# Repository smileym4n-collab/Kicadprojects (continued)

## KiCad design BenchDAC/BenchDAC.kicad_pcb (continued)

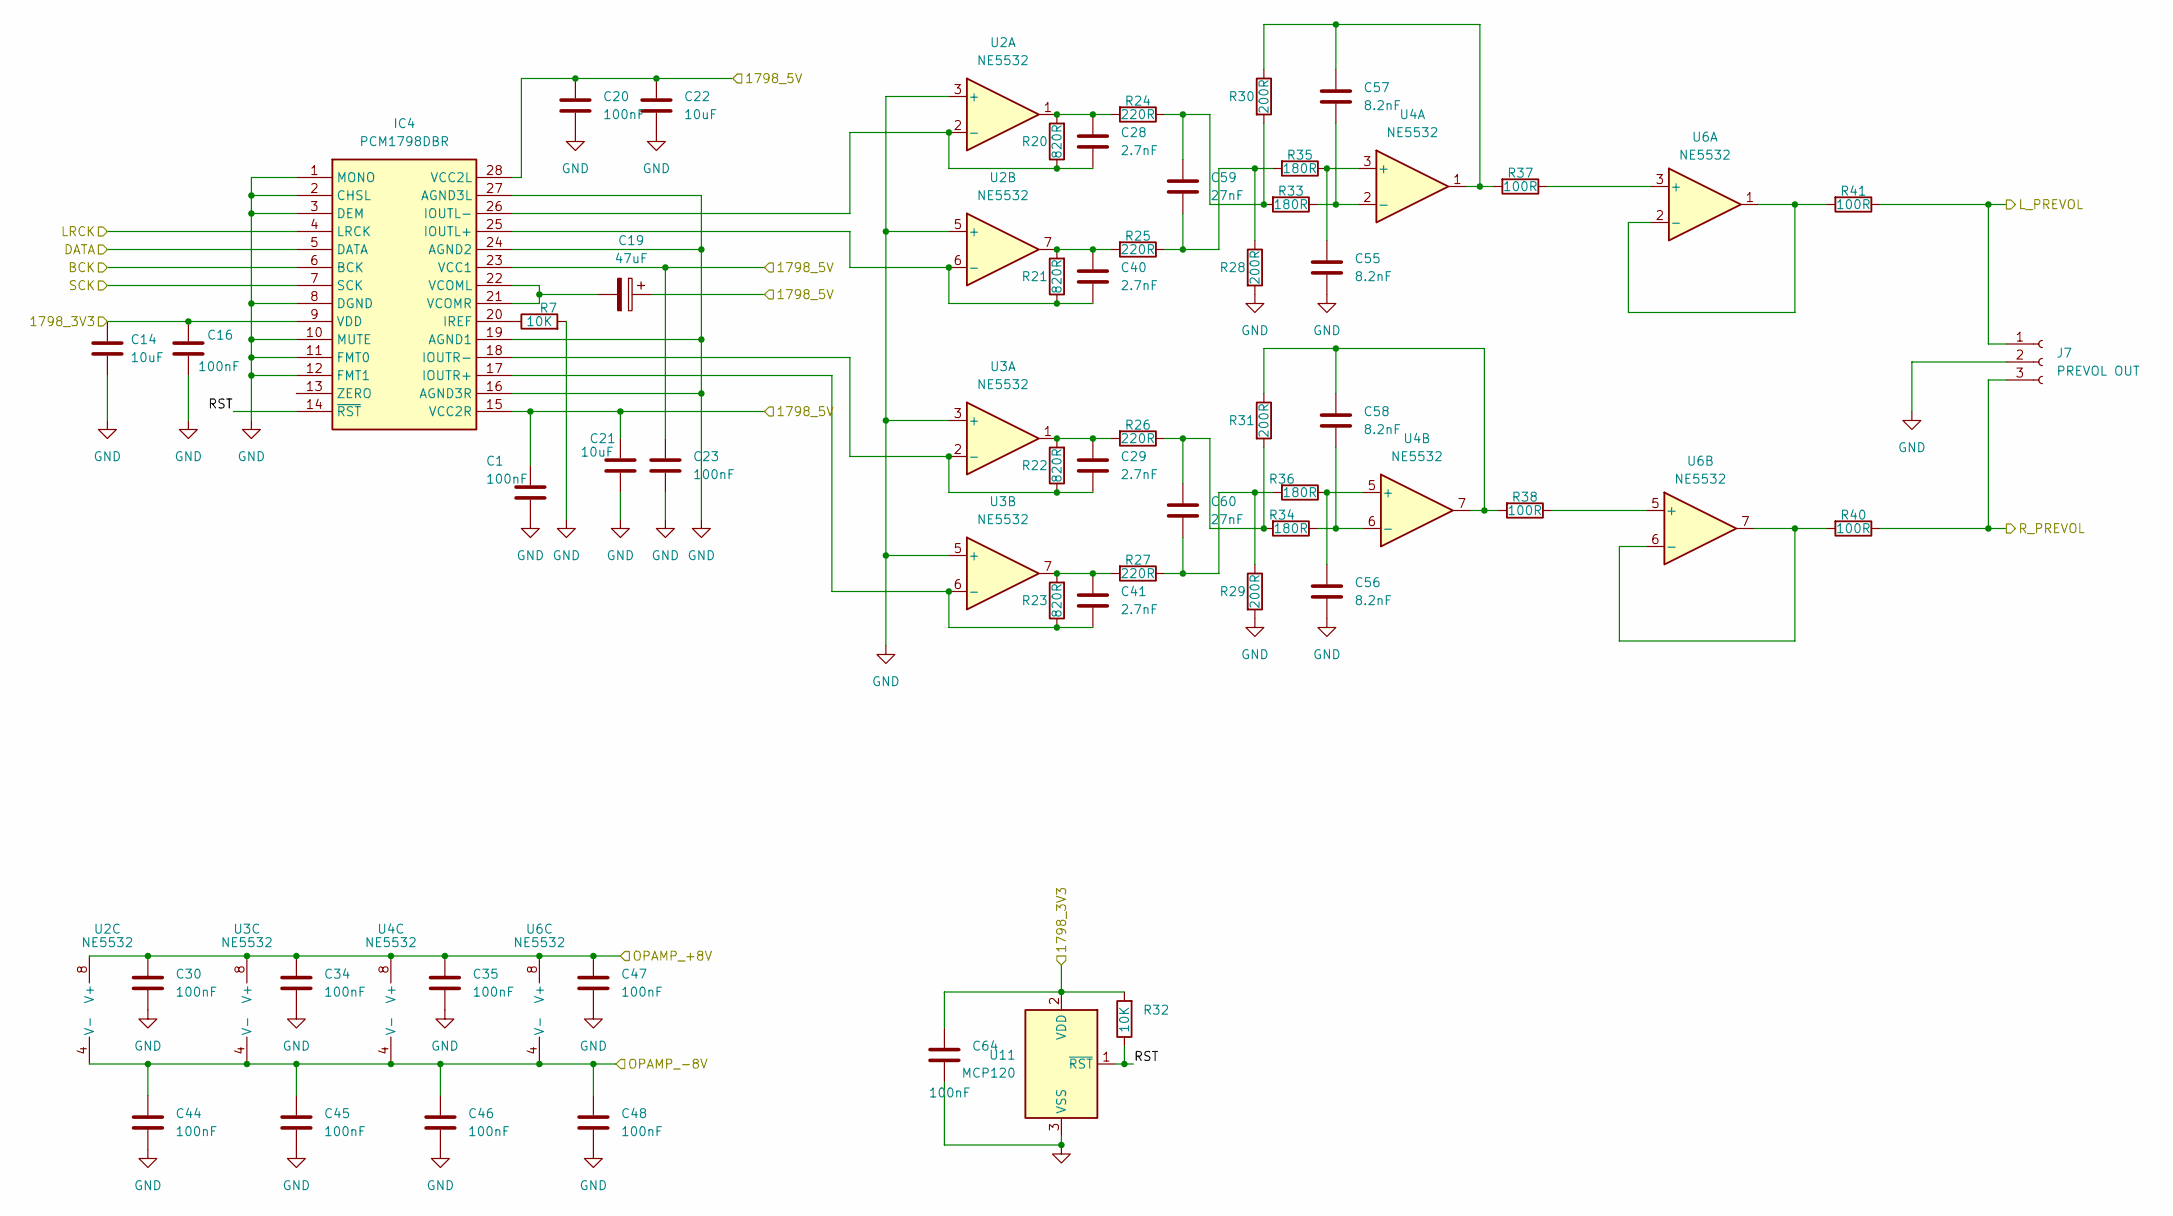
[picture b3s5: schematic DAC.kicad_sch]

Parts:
C1, C16, C20, C23, C30, C34, C35, C44, C45, C46, C47, C48, C64: 100nF; C_0603_1608Metric_Pad1.08x0.95mm_HandSolder
C14, C21, C22: 10uF; C_0805_2012Metric_Pad1.18x1.45mm_HandSolder
C19: 47uF; CP_Radial_D6.3mm_P2.50mm
C28, C29, C40, C41: 2.7nF; C_0805_2012Metric_Pad1.18x1.45mm_HandSolder
C55, C56, C57, C58: 8.2nF; C_0805_2012Metric_Pad1.18x1.45mm_HandSolder
C59, C60: 27nF; C_1206_3216Metric_Pad1.33x1.80mm_HandSolder
IC4: PCM1798DBR; SOP65P780X200-28N; Mouser Part Number 595-PCM1798DBR
J7: PREVOL OUT; JST_XH_B3B-XH-A_1x03_P2.50mm_Vertical
R7: 10K; R_0603_1608Metric_Pad0.98x0.95mm_HandSolder
R20, R21, R22, R23: 820R; R_0805_2012Metric_Pad1.20x1.40mm_HandSolder
R24, R25, R26, R27: 220R; R_0805_2012Metric_Pad1.20x1.40mm_HandSolder
R28, R29, R30, R31: 200R; R_0805_2012Metric_Pad1.20x1.40mm_HandSolder
R32: 10K; R_0805_2012Metric_Pad1.20x1.40mm_HandSolder
R33, R34, R35, R36: 180R; R_0805_2012Metric_Pad1.20x1.40mm_HandSolder
R37, R38, R40, R41: 100R; R_0805_2012Metric_Pad1.20x1.40mm_HandSolder
U2, U3, U4, U6: NE5532; SOIC-8_3.9x4.9mm_P1.27mm
U11: MCP120; SOT-23

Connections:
/DAC/1798_3V3: C14.1, C16.1, C64.2, IC4.9 (VDD), R32.2, U11.2 (VDD); also elsewhere on the board
/DAC/1798_5V: C1.1, C19.1, C20.1, C21.1, C22.1, C23.1, IC4.15 (VCC2R), IC4.23 (VCC1), IC4.28 (VCC2L); also elsewhere on the board
/DAC/BCK: IC4.6 (BCK); also elsewhere on the board
/DAC/DATA: IC4.5 (DATA); also elsewhere on the board
/DAC/LRCK: IC4.4 (LRCK); also elsewhere on the board
/DAC/L_PREVOL: J7.1, R41.1; also elsewhere on the board
/DAC/OPAMP_+8V: C30.1, C34.1, C35.1, C47.1, U2.8 (V+), U3.8 (V+), U4.8 (V+), U6.8 (V+); also elsewhere on the board
/DAC/OPAMP_-8V: C44.1, C45.1, C46.1, C48.1, U2.4 (V-), U3.4 (V-), U4.4 (V-), U6.4 (V-); also elsewhere on the board
/DAC/RST: IC4.14 (~RST), R32.1, U11.1 (~RST)
/DAC/R_PREVOL: J7.3, R40.1; also elsewhere on the board
/DAC/SCK: IC4.7 (SCK); also elsewhere on the board
GND: C1.2, C14.2, C16.2, C20.2, C21.2, C22.2, C23.2, C30.2, C34.2, C35.2, C44.2, C45.2, C46.2, C47.2, C48.2, C55.2, C56.2, C64.1, IC4.1 (MONO), IC4.2 (CHSL), IC4.3 (DEM), IC4.8 (DGND), IC4.10 (MUTE), IC4.11 (FMT0), IC4.12 (FMT1), IC4.16 (AGND3R), IC4.19 (AGND1), IC4.24 (AGND2), IC4.27 (AGND3L), J7.2, R7.2, R28.2, R29.2, U2.3 (+), U2.5 (+), U3.3 (+), U3.5 (+), U11.3 (VSS); also elsewhere on the board
unnamed: C28.2, R20.2, R24.2, U2.1
unnamed: C29.2, R22.2, R26.2, U3.1
unnamed: C40.2, R21.2, R25.2, U2.7
unnamed: C41.2, R23.2, R27.2, U3.7
unnamed: C57.1, R30.1, R37.2, U4.1
unnamed: C58.1, R31.1, R38.2, U4.7
unnamed: C59.1, R24.1, R30.2, R33.2
unnamed: C59.2, R25.1, R28.1, R35.2
unnamed: C60.1, R26.1, R31.2, R34.2
unnamed: C60.2, R27.1, R29.1, R36.2
unnamed: C40.1, IC4.25 (IOUTL+), R21.1, U2.6 (-)
unnamed: C28.1, IC4.26 (IOUTL-), R20.1, U2.2 (-)
unnamed: C41.1, IC4.17 (IOUTR+), R23.1, U3.6 (-)
unnamed: C29.1, IC4.18 (IOUTR-), R22.1, U3.2 (-)
unnamed: IC4.20 (IREF), R7.1
unnamed: C19.2, IC4.21 (VCOMR), IC4.22 (VCOML)
unnamed: C55.1, R35.1, U4.3 (+)
unnamed: C57.2, R33.1, U4.2 (-)
unnamed: C56.1, R36.1, U4.5 (+)
unnamed: C58.2, R34.1, U4.6 (-)
unnamed: R37.1, U6.3 (+)
unnamed: R41.2, U6.1, U6.2 (-)
unnamed: R38.1, U6.5 (+)
unnamed: R40.2, U6.6 (-), U6.7

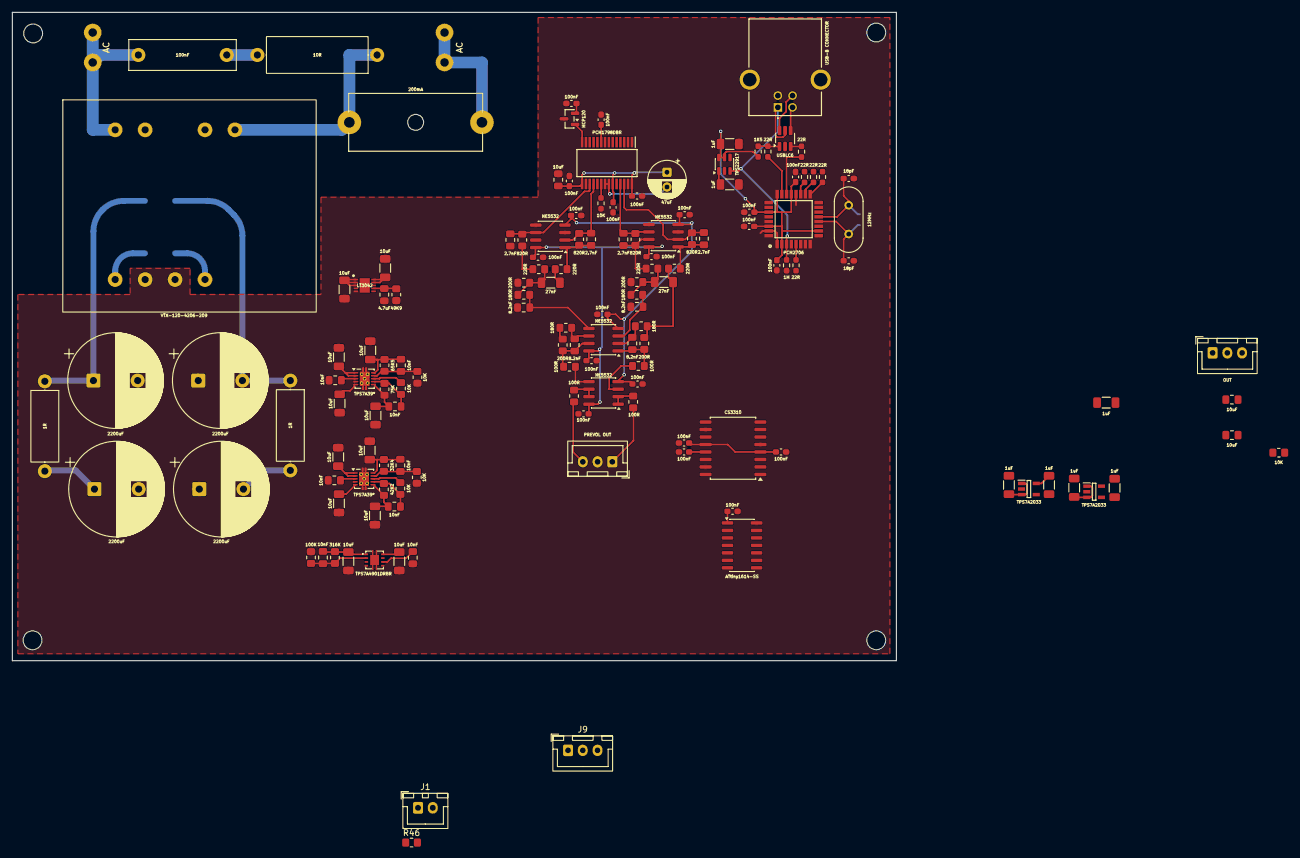
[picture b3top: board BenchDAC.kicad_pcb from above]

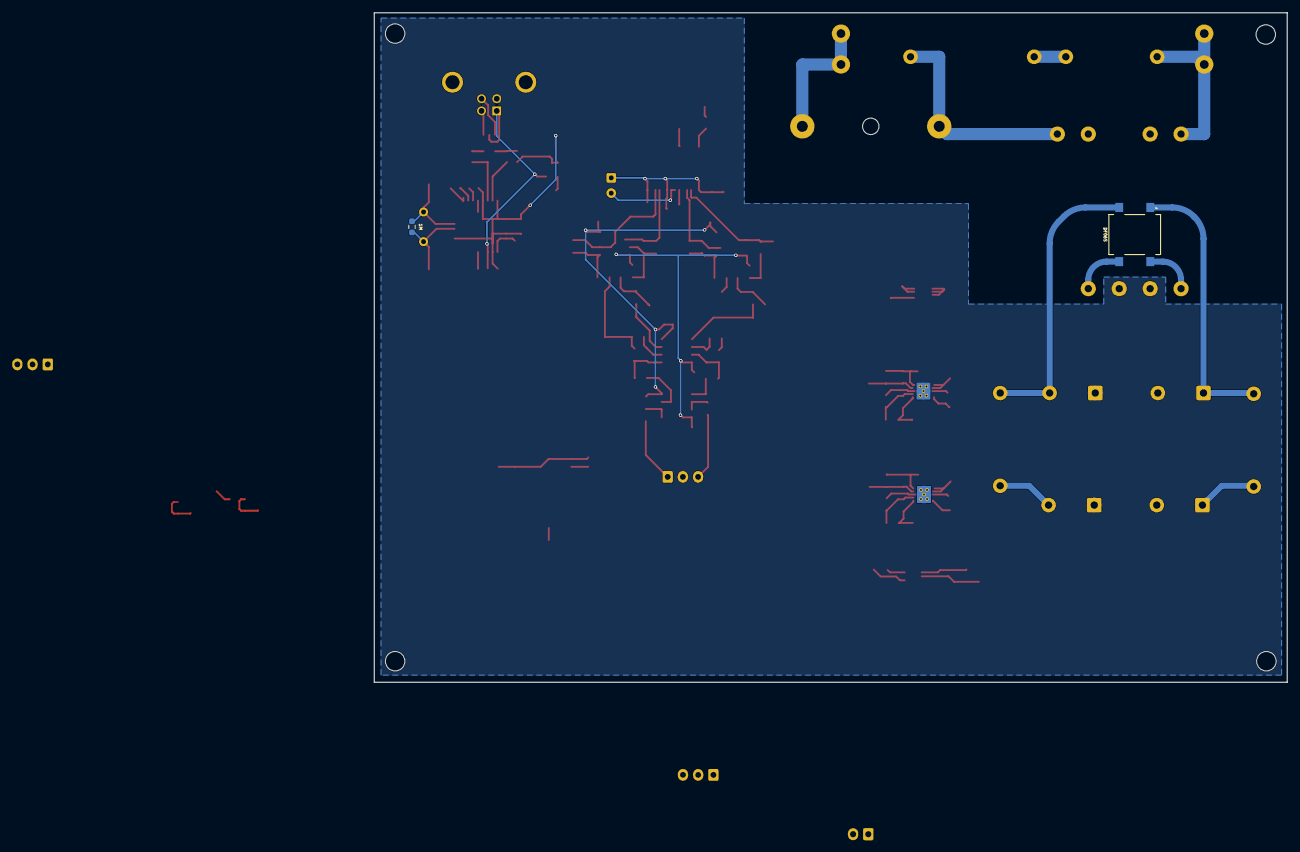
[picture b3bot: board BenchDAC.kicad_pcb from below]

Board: 2 copper layers, 150.0 x 110.0 mm, 148 parts (2 on the bottom side), 79 nets.

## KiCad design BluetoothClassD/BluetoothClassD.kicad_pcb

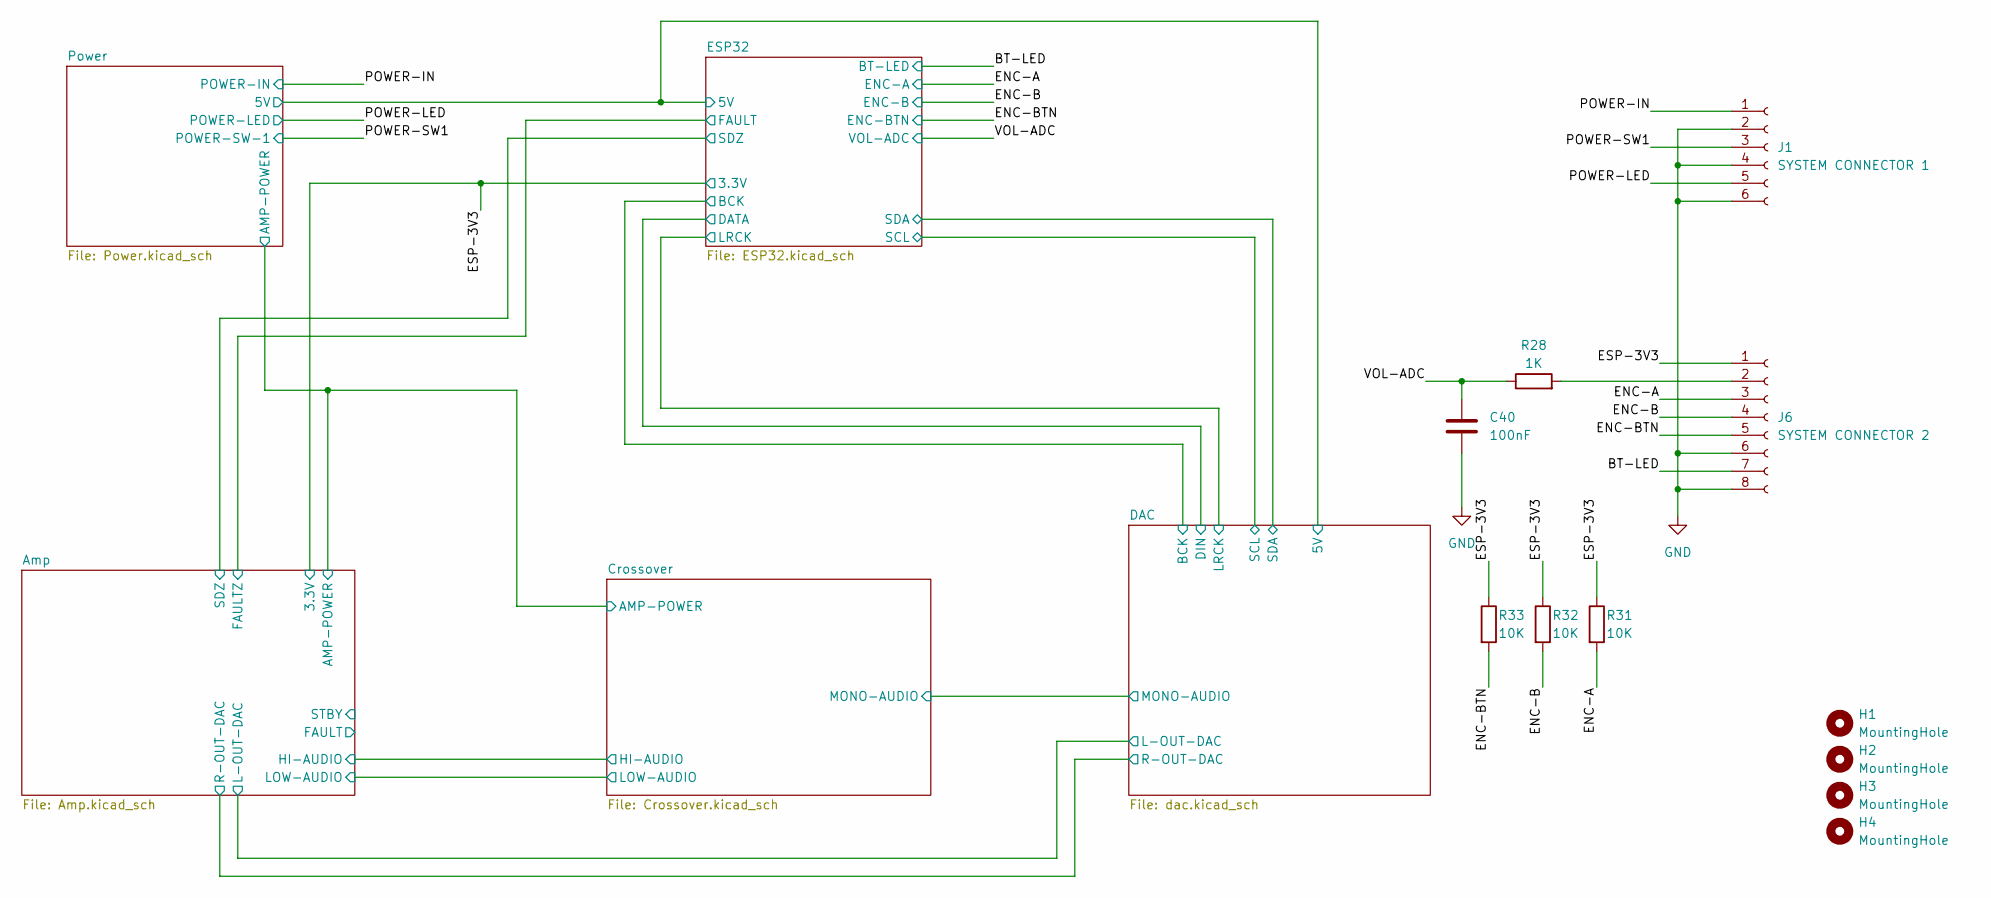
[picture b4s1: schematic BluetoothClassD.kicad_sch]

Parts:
C40: 100nF; C_1206_3216Metric_Pad1.33x1.80mm_HandSolder
H1, H2, H3, H4: MountingHole; MountingHole_4.3mm_M4
J1: SYSTEM CONNECTOR 1; JST_XH_B6B-XH-A_1x06_P2.50mm_Vertical
J6: SYSTEM CONNECTOR 2; JST_XH_B8B-XH-A_1x08_P2.50mm_Vertical
R28: 1K; R_0805_2012Metric_Pad1.20x1.40mm_HandSolder
R31, R32, R33: 10K; R_0603_1608Metric_Pad0.98x0.95mm_HandSolder

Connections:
/BT-LED: J6.7; also elsewhere on the board
/ENC-A: J6.3, R31.2; also elsewhere on the board
/ENC-B: J6.4, R32.2; also elsewhere on the board
/ENC-BTN: J6.5, R33.2; also elsewhere on the board
/ESP-3V3: J6.1, R31.1, R32.1, R33.1; also elsewhere on the board
/POWER-IN: J1.1; also elsewhere on the board
/POWER-LED: J1.5; also elsewhere on the board
/POWER-SW1: J1.3; also elsewhere on the board
/VOL-ADC: C40.1, R28.1; also elsewhere on the board
GND: C40.2, J1.2, J1.4, J1.6, J6.6, J6.8; also elsewhere on the board
unnamed: J6.2, R28.2

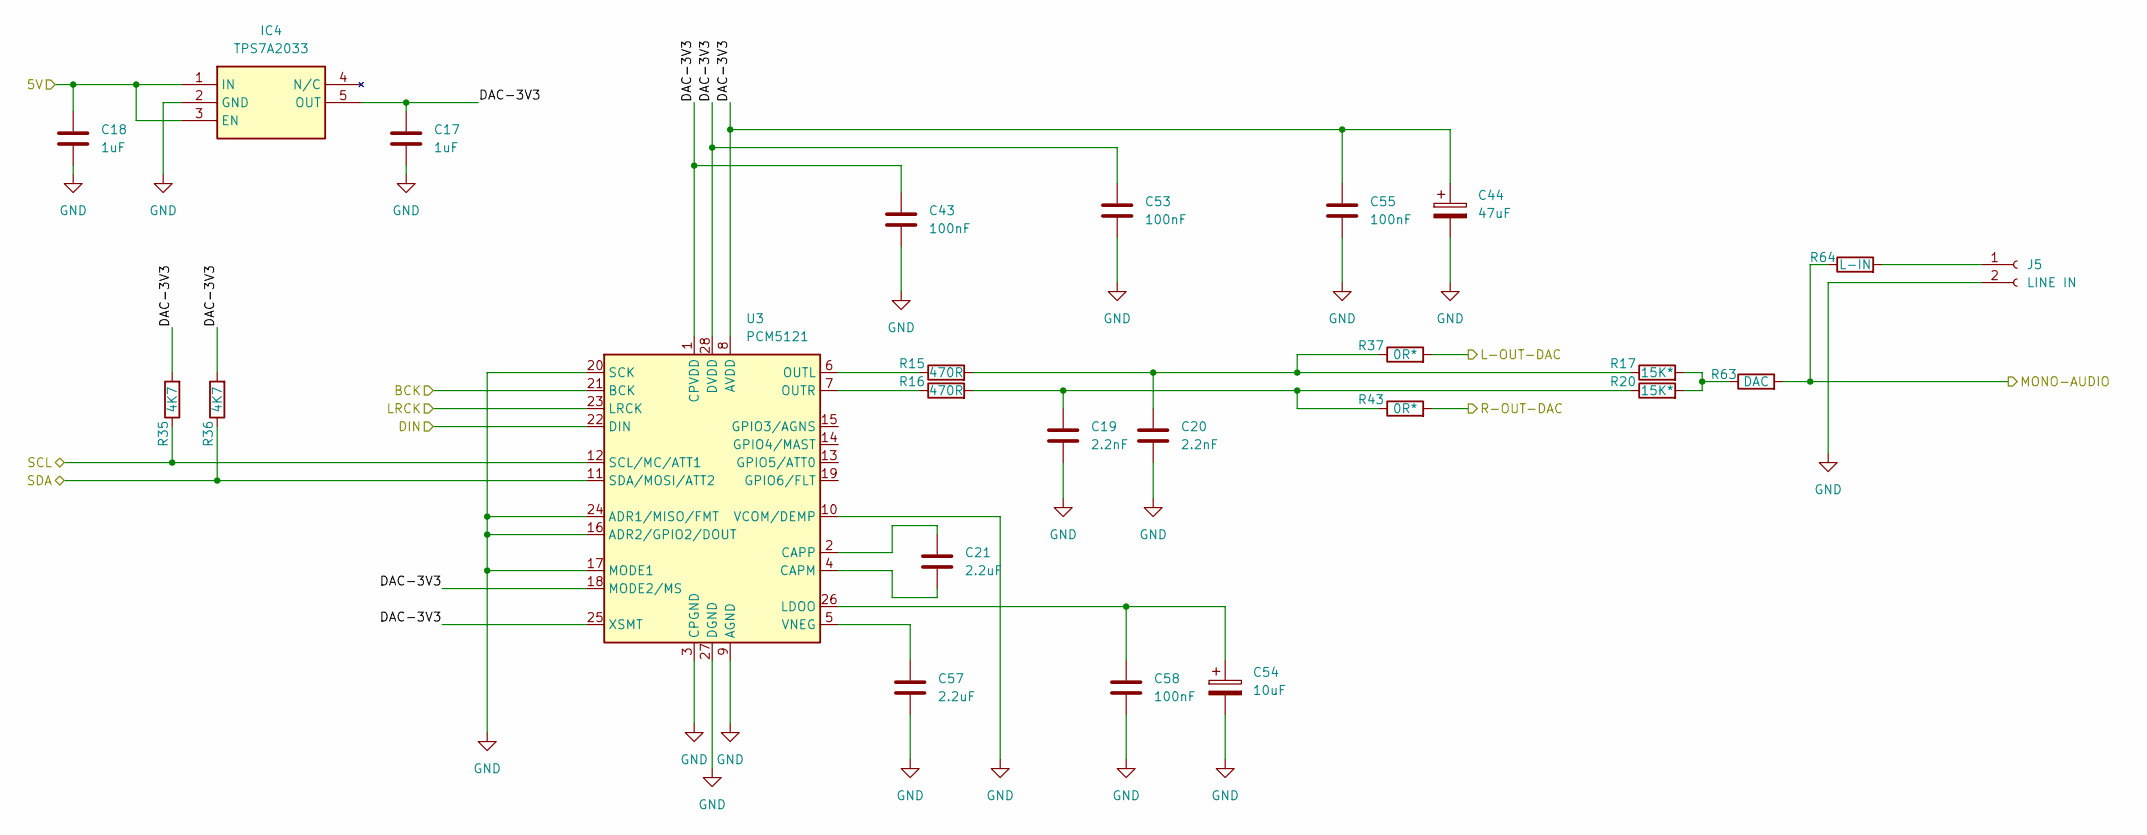
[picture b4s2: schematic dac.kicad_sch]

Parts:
C17, C18: 1uF; C_1206_3216Metric_Pad1.33x1.80mm_HandSolder
C19, C20: 2.2nF; C_0805_2012Metric_Pad1.18x1.45mm_HandSolder
C21, C57: 2.2uF; C_0805_2012Metric_Pad1.18x1.45mm_HandSolder
C43, C53, C55, C58: 100nF; C_1206_3216Metric_Pad1.33x1.80mm_HandSolder
C44: 47uF; CP_Radial_D8.0mm_P2.50mm
C54: 10uF; CP_Radial_D4.0mm_P2.00mm
IC4: TPS7A2033; SOT95P280X145-5N; Mouser Part Number 595-TPS7A2033PDBVR
J5: LINE IN; JST_XH_B2B-XH-A_1x02_P2.50mm_Vertical
R15, R16: 470R; R_0805_2012Metric_Pad1.20x1.40mm_HandSolder
R17, R20: 15K*; R_0805_2012Metric_Pad1.20x1.40mm_HandSolder
R35, R36: 4K7; R_0805_2012Metric_Pad1.20x1.40mm_HandSolder
R37, R43: 0R*; R_0805_2012Metric_Pad1.20x1.40mm_HandSolder
R63: DAC; R_0805_2012Metric_Pad1.20x1.40mm_HandSolder
R64: L-IN; R_0805_2012Metric_Pad1.20x1.40mm_HandSolder
U3: PCM5121; TSSOP-28_4.4x9.7mm_P0.65mm

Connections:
/Amp/HI-AUDIO: R37.2; also elsewhere on the board
/Amp/LOW-AUDIO: R43.2; also elsewhere on the board
/Crossover/MONO-AUDIO: R63.2, R64.1; also elsewhere on the board
/DAC/5V: C18.1, IC4.1 (IN), IC4.3 (EN); also elsewhere on the board
/DAC/BCK: U3.21 (BCK); also elsewhere on the board
/DAC/DAC-3V3: C17.1, C43.1, C44.1, C53.1, C55.1, IC4.5 (OUT), R35.2, R36.2, U3.1 (CPVDD), U3.8 (AVDD), U3.18 (MODE2/MS), U3.25 (XSMT), U3.28 (DVDD)
/DAC/DIN: U3.22 (DIN); also elsewhere on the board
/DAC/LRCK: U3.23 (LRCK); also elsewhere on the board
/DAC/SCL: R35.1, U3.12 (SCL/MC/ATT1); also elsewhere on the board
/DAC/SDA: R36.1, U3.11 (SDA/MOSI/ATT2); also elsewhere on the board
GND: C17.2, C18.2, C19.2, C20.2, C43.2, C44.2, C53.2, C54.2, C55.2, C57.2, C58.2, IC4.2 (GND), J5.2, U3.3 (CPGND), U3.9 (AGND), U3.10 (VCOM/DEMP), U3.16 (ADR2/GPIO2/DOUT), U3.17 (MODE1), U3.20 (SCK), U3.24 (ADR1/MISO/FMT), U3.27 (DGND); also elsewhere on the board
unnamed: C19.1, R16.2, R20.1, R43.1
unnamed: C20.1, R15.2, R17.1, R37.1
unnamed: J5.1, R64.2
unnamed: R17.2, R20.2, R63.1
unnamed: C21.2, U3.4 (CAPM)
unnamed: C21.1, U3.2 (CAPP)
unnamed: C54.1, C58.1, U3.26 (LDOO)
unnamed: R15.1, U3.6 (OUTL)
unnamed: R16.1, U3.7 (OUTR)
unnamed: C57.1, U3.5 (VNEG)

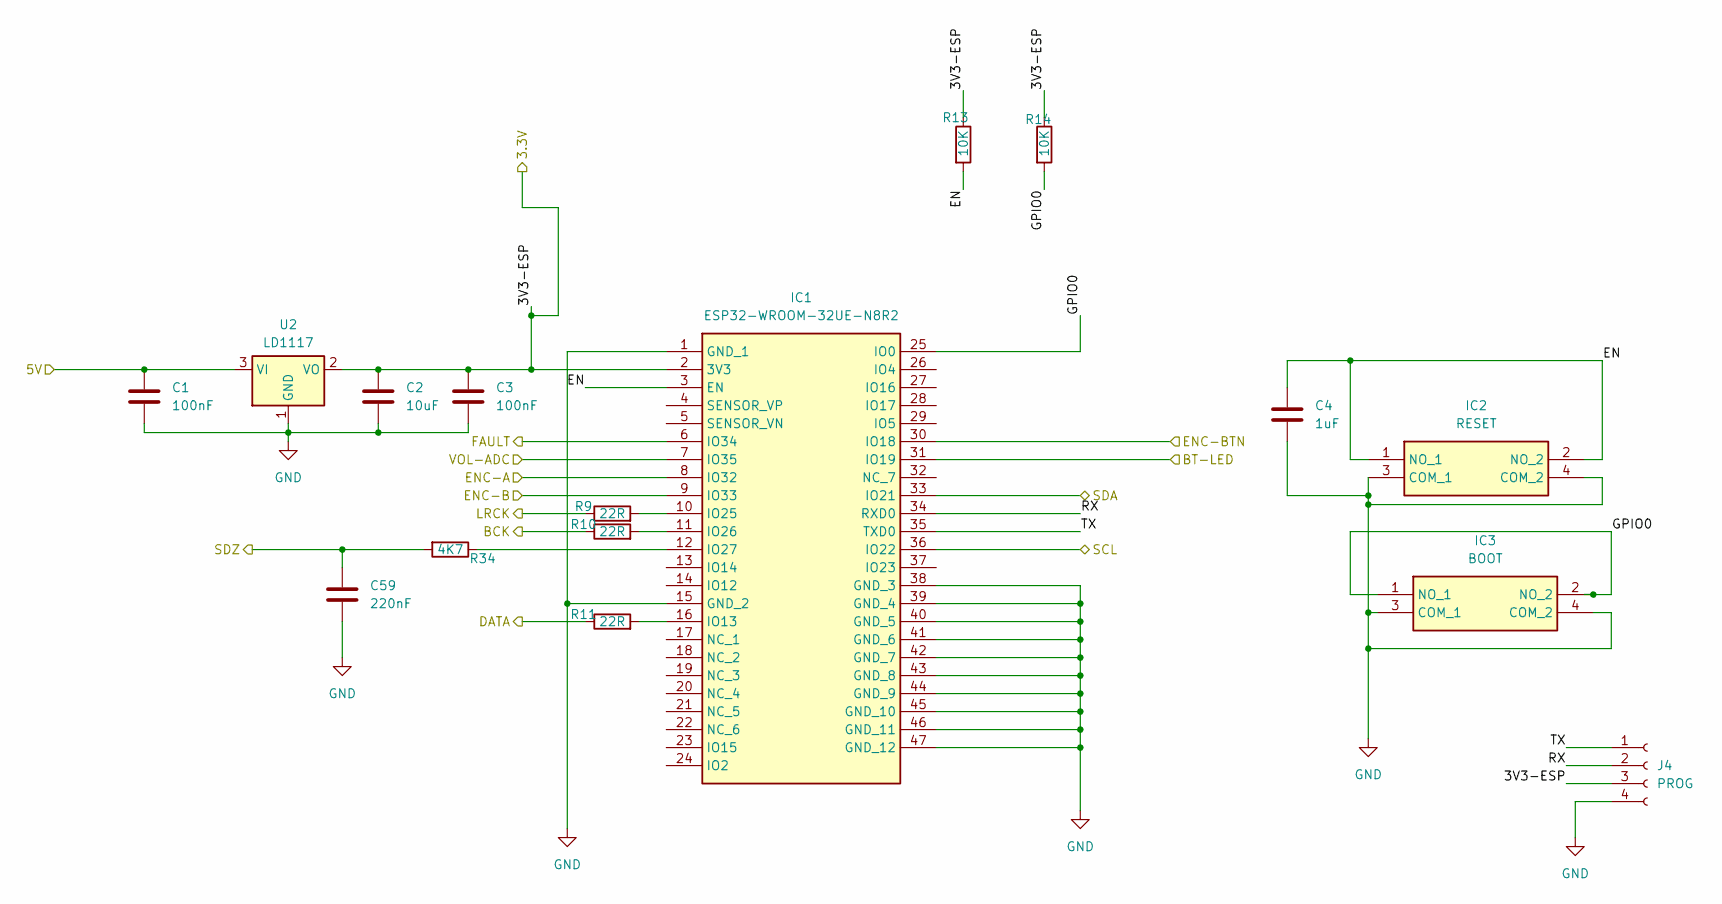
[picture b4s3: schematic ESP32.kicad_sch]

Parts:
C1, C3: 100nF; C_1206_3216Metric_Pad1.33x1.80mm_HandSolder
C2: 10uF; C_0805_2012Metric_Pad1.18x1.45mm_HandSolder
C4: 1uF; C_1206_3216Metric_Pad1.33x1.80mm_HandSolder
C59: 220nF; C_0805_2012Metric_Pad1.18x1.45mm_HandSolder
IC1: ESP32-WROOM-32UE-N8R2; ESP32WROOM32UEN8R2; Mouser Part Number 356-ESP32WRM32UEN8R2
IC2: RESET; TS026650BK100SCRD; Mouser Part Number 179-TS026650BK100SCR
IC3: BOOT; TS026650BK100SCRD; Mouser Part Number 179-TS026650BK100SCR
J4: PROG; PinHeader_1x04_P2.54mm_Vertical
R9, R10, R11: 22R; R_0603_1608Metric_Pad0.98x0.95mm_HandSolder
R13, R14: 10K; R_0603_1608Metric_Pad0.98x0.95mm_HandSolder
R34: 4K7; R_0805_2012Metric_Pad1.20x1.40mm_HandSolder
U2: LD1117; SOT-223-3_TabPin2

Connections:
/Amp/FAULTZ: IC1.6 (IO34); also elsewhere on the board
/Amp/SDZ: C59.1, R34.2; also elsewhere on the board
/BT-LED: IC1.31 (IO19); also elsewhere on the board
/DAC/5V: C1.1, U2.3 (VI); also elsewhere on the board
/DAC/BCK: R10.1; also elsewhere on the board
/DAC/DIN: R11.1; also elsewhere on the board
/DAC/LRCK: R9.1; also elsewhere on the board
/DAC/SCL: IC1.36 (IO22); also elsewhere on the board
/DAC/SDA: IC1.33 (IO21); also elsewhere on the board
/ENC-A: IC1.8 (IO32); also elsewhere on the board
/ENC-B: IC1.9 (IO33); also elsewhere on the board
/ENC-BTN: IC1.30 (IO18); also elsewhere on the board
/ESP32/EN: C4.1, IC1.3 (EN), IC2.1 (NO_1), IC2.2 (NO_2), R13.2
/ESP32/GPIO0: IC1.25 (IO0), IC3.1 (NO_1), IC3.2 (NO_2), R14.2
/ESP32/RX: IC1.34 (RXD0), J4.2
/ESP32/TX: IC1.35 (TXD0), J4.1
/ESP-3V3: C2.1, C3.1, IC1.2 (3V3), J4.3, R13.1, R14.1, U2.2 (VO); also elsewhere on the board
/VOL-ADC: IC1.7 (IO35); also elsewhere on the board
GND: C1.2, C2.2, C3.2, C4.2, C59.2, IC1.1 (GND_1), IC1.15 (GND_2), IC1.38 (GND_3), IC1.39 (GND_4), IC1.40 (GND_5), IC1.41 (GND_6), IC1.42 (GND_7), IC1.43 (GND_8), IC1.44 (GND_9), IC1.45 (GND_10), IC1.46 (GND_11), IC1.47 (GND_12), IC2.3 (COM_1), IC2.4 (COM_2), IC3.3 (COM_1), IC3.4 (COM_2), J4.4, U2.1 (GND); also elsewhere on the board
unnamed: IC1.16 (IO13), R11.2
unnamed: IC1.10 (IO25), R9.2
unnamed: IC1.11 (IO26), R10.2
unnamed: IC1.12 (IO27), R34.1

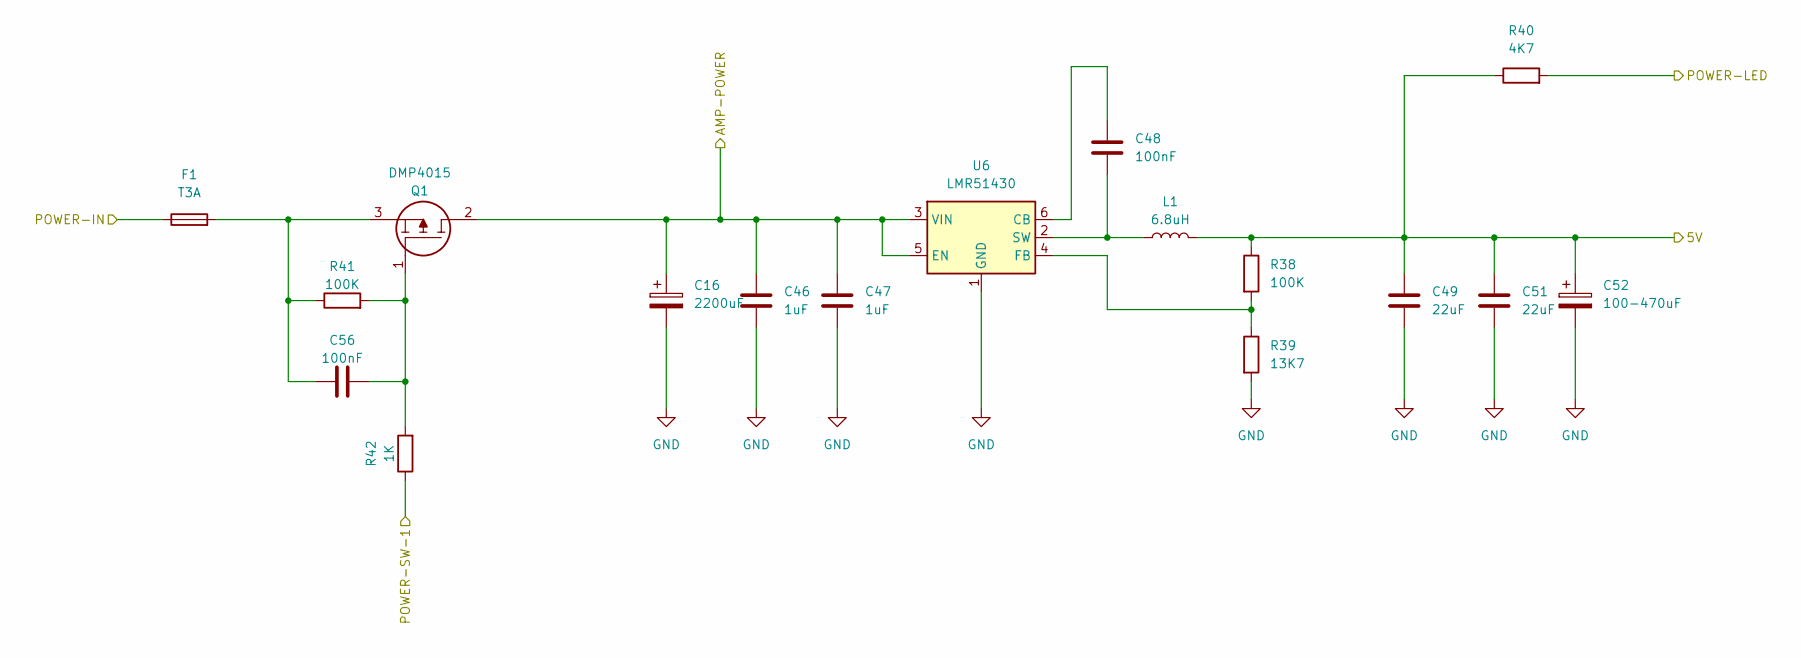
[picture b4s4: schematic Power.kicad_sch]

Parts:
C16: 2200uF; CP_Radial_D16.0mm_P7.50mm
C46, C47: 1uF; C_1206_3216Metric_Pad1.33x1.80mm_HandSolder
C48, C56: 100nF; C_1206_3216Metric_Pad1.33x1.80mm_HandSolder
C49, C51: 22uF; C_1206_3216Metric_Pad1.33x1.80mm_HandSolder
C52: 100-470uF; CP_Radial_D8.0mm_P3.50mm
F1: T3A; Fuse_1206_3216Metric_Pad1.42x1.75mm_HandSolder
L1: 6.8uH; SRP6030WA-6R8M
Q1: DMP4015; DMP4015SK313; Manufacturer_Part_Number DMP4015SK3-13
R38, R41: 100K; R_0805_2012Metric_Pad1.20x1.40mm_HandSolder
R39: 13K7; R_0805_2012Metric_Pad1.20x1.40mm_HandSolder
R40: 4K7; R_0805_2012Metric_Pad1.20x1.40mm_HandSolder
R42: 1K; R_0805_2012Metric_Pad1.20x1.40mm_HandSolder
U6: LMR51430; SOT-23-6_Handsoldering

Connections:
/Amp/PVCC: C16.1, C46.1, C47.1, Q1.2, U6.3 (VIN), U6.5 (EN); also elsewhere on the board
/DAC/5V: C49.1, C51.1, C52.1, L1.2, R38.1, R40.1; also elsewhere on the board
/POWER-IN: F1.1; also elsewhere on the board
/POWER-LED: R40.2; also elsewhere on the board
/POWER-SW1: R42.1; also elsewhere on the board
GND: C16.2, C46.2, C47.2, C49.2, C51.2, C52.2, R39.2, U6.1 (GND); also elsewhere on the board
unnamed: C56.1, F1.2, Q1.3, R41.1
unnamed: C56.2, Q1.1, R41.2, R42.2
unnamed: C48.1, U6.6 (CB)
unnamed: R38.2, R39.1, U6.4 (FB)
unnamed: C48.2, L1.1, U6.2 (SW)

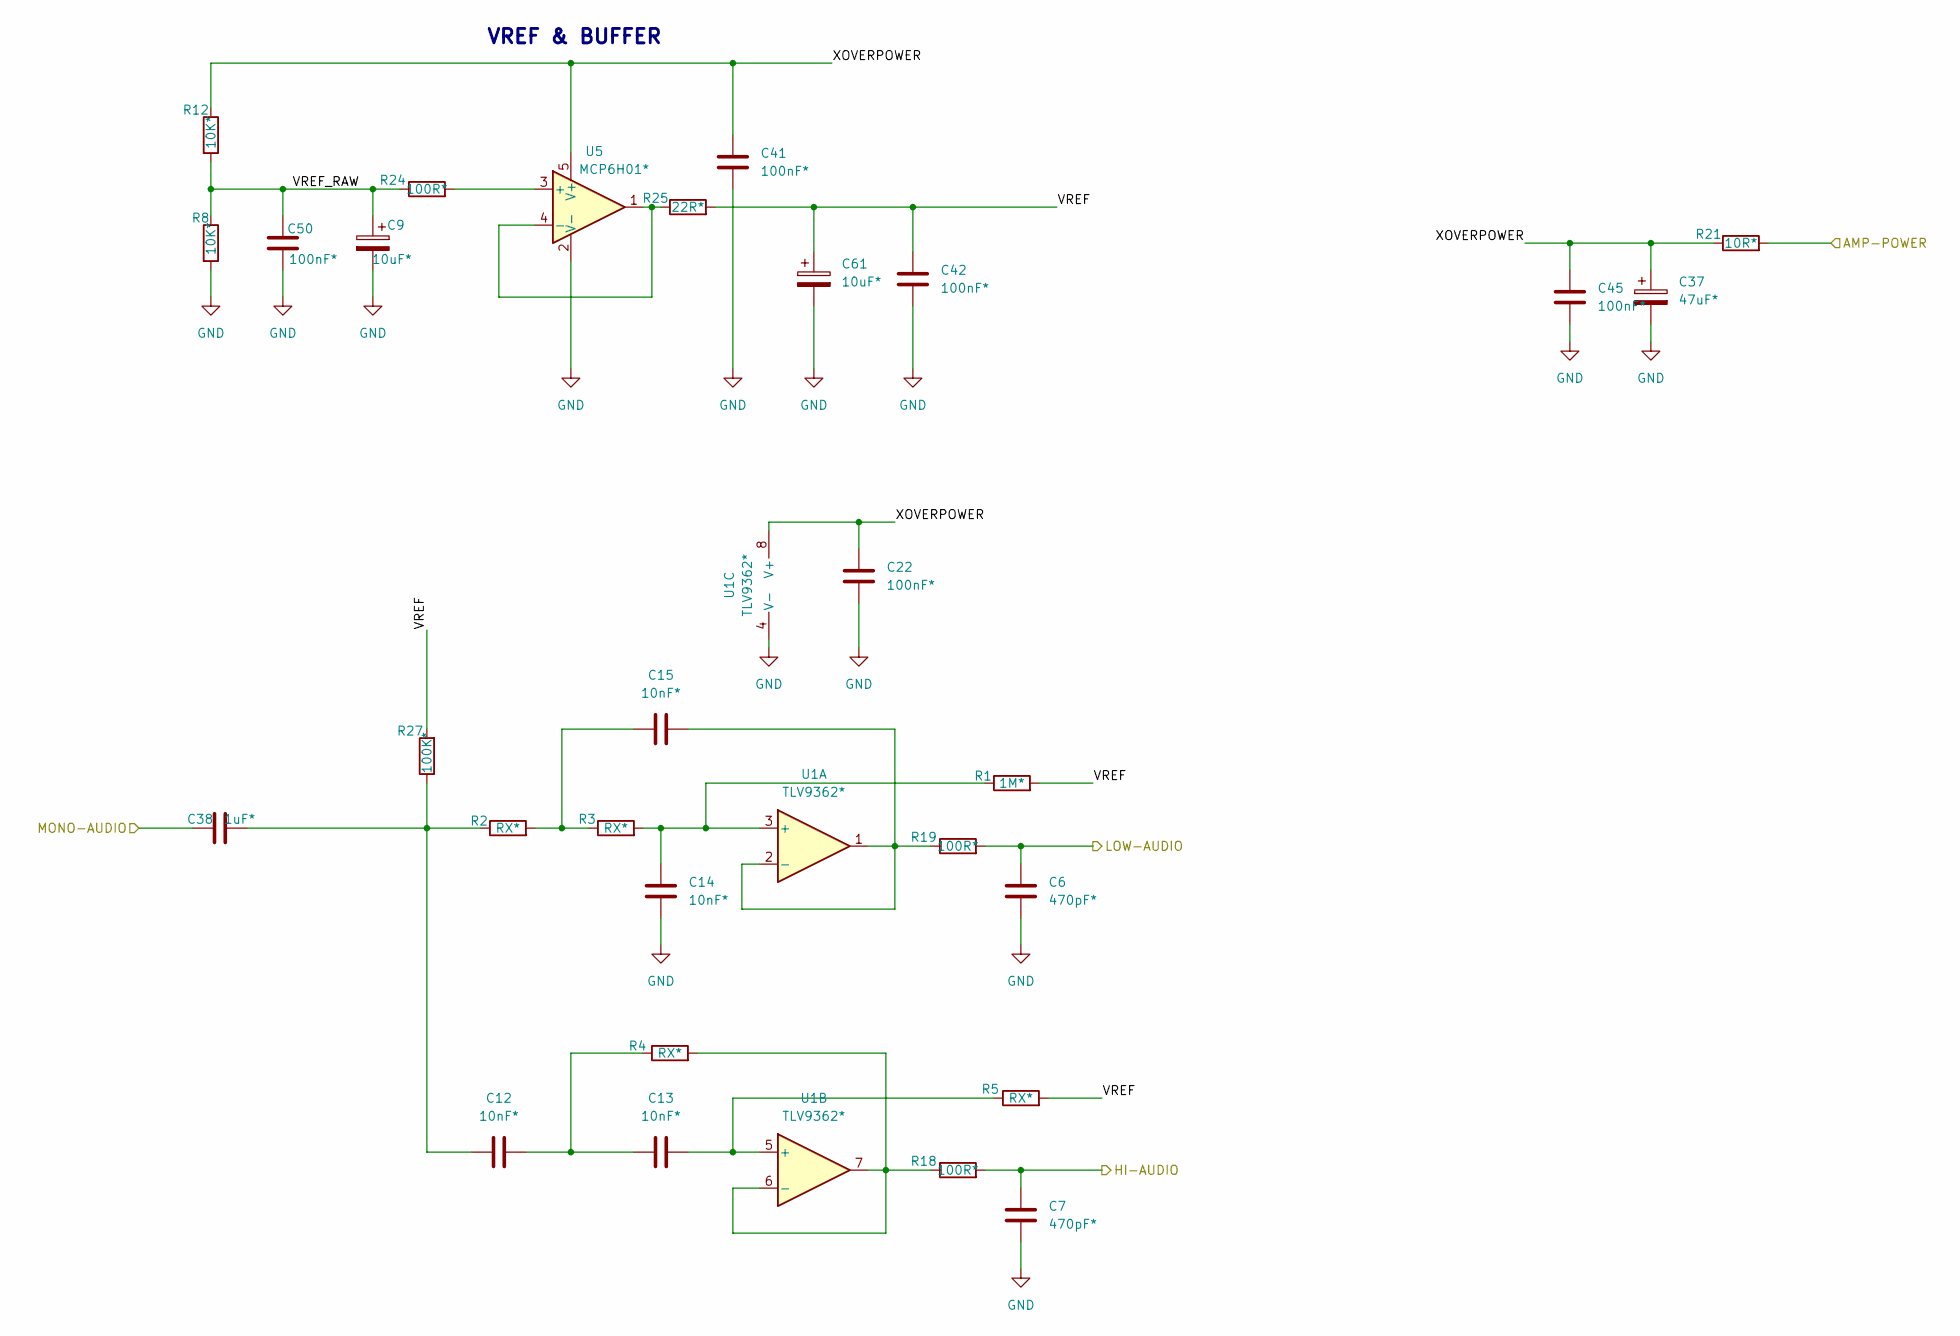
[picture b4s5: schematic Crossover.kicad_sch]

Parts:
C6, C7: 470pF*; C_0805_2012Metric_Pad1.18x1.45mm_HandSolder
C9, C61: 10uF*; CP_Radial_D4.0mm_P1.50mm
C12, C13, C14, C15: 10nF*; C_0805_2012Metric_Pad1.18x1.45mm_HandSolder
C22, C41, C42, C45, C50: 100nF*; C_1206_3216Metric_Pad1.33x1.80mm_HandSolder
C37: 47uF*; CP_Radial_D5.0mm_P2.50mm
C38: 1uF*; C_Rect_L7.2mm_W5.5mm_P5.00mm_FKS2_FKP2_MKS2_MKP2
R1: 1M*; R_0805_2012Metric_Pad1.20x1.40mm_HandSolder
R2, R3, R4, R5: RX*; R_0805_2012Metric_Pad1.20x1.40mm_HandSolder
R8, R12: 10K*; R_0805_2012Metric_Pad1.20x1.40mm_HandSolder
R18, R19, R24: 100R*; R_0805_2012Metric_Pad1.20x1.40mm_HandSolder
R21: 10R*; R_0805_2012Metric_Pad1.20x1.40mm_HandSolder
R25: 22R*; R_0805_2012Metric_Pad1.20x1.40mm_HandSolder
R27: 100K*; R_0805_2012Metric_Pad1.20x1.40mm_HandSolder
U1: TLV9362*; SOIC-8_3.9x4.9mm_P1.27mm
U5: MCP6H01*; SOT-23-5

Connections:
/Amp/HI-AUDIO: C7.1, R18.2; also elsewhere on the board
/Amp/LOW-AUDIO: C6.1, R19.2; also elsewhere on the board
/Amp/PVCC: R21.2; also elsewhere on the board
/Crossover/MONO-AUDIO: C38.1; also elsewhere on the board
/Crossover/VREF: C42.1, C61.1, R1.2, R5.2, R25.2, R27.2
/Crossover/VREF_RAW: C9.1, C50.2, R8.1, R12.2, R24.1
/Crossover/XOVERPOWER: C22.1, C37.1, C41.1, C45.1, R12.1, R21.1, U1.8 (V+), U5.5 (V+)
GND: C6.2, C7.2, C9.2, C14.2, C22.2, C37.2, C41.2, C42.2, C45.2, C50.1, C61.2, R8.2, U1.4 (V-), U5.2 (V-); also elsewhere on the board
unnamed: C12.1, C38.2, R2.1, R27.1
unnamed: C12.2, C13.1, R4.1
unnamed: C15.1, R2.2, R3.1
unnamed: C14.1, R1.1, R3.2, U1.3 (+)
unnamed: C15.2, R19.1, U1.1, U1.2 (-)
unnamed: C13.2, R5.1, U1.5 (+)
unnamed: R4.2, R18.1, U1.6 (-), U1.7
unnamed: R24.2, U5.3 (+)
unnamed: R25.1, U5.1, U5.4 (-)

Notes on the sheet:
VREF & BUFFER
